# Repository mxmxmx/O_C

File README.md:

o_C. polymorphic CV generator
===

### firmware:

o_C is a collaborative project by Patrick Dowling (aka pld), mxmxmx and Tim Churches (aka bennelong.bicyclist) (though mostly by pld and bennelong.bicyclist). it **(considerably) extends** the original firmware for the o_C / ASR eurorack module, designed by mxmxmx.

### hardware:

eurorack / teensy 3.2 DAC8565 quad 16bit CV module w/ OLED display

14HP, depth ~ 25mm

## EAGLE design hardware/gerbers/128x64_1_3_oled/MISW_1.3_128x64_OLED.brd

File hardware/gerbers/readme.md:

CAM files for teensy 3.x quad 16 bit CV generator/processor
============

###gerbers for:

- O_C main pcb (2.e)
- SSD1306 / SH1106 OLED carrier pcb (thanks, altitude909)

###BOM for OLED carrier pcb

(all 0603): 

- 4 x 10k 
- 1 x 390K 
- 5 x 2.2uF (10V)
- 1 x 10uF (10V)

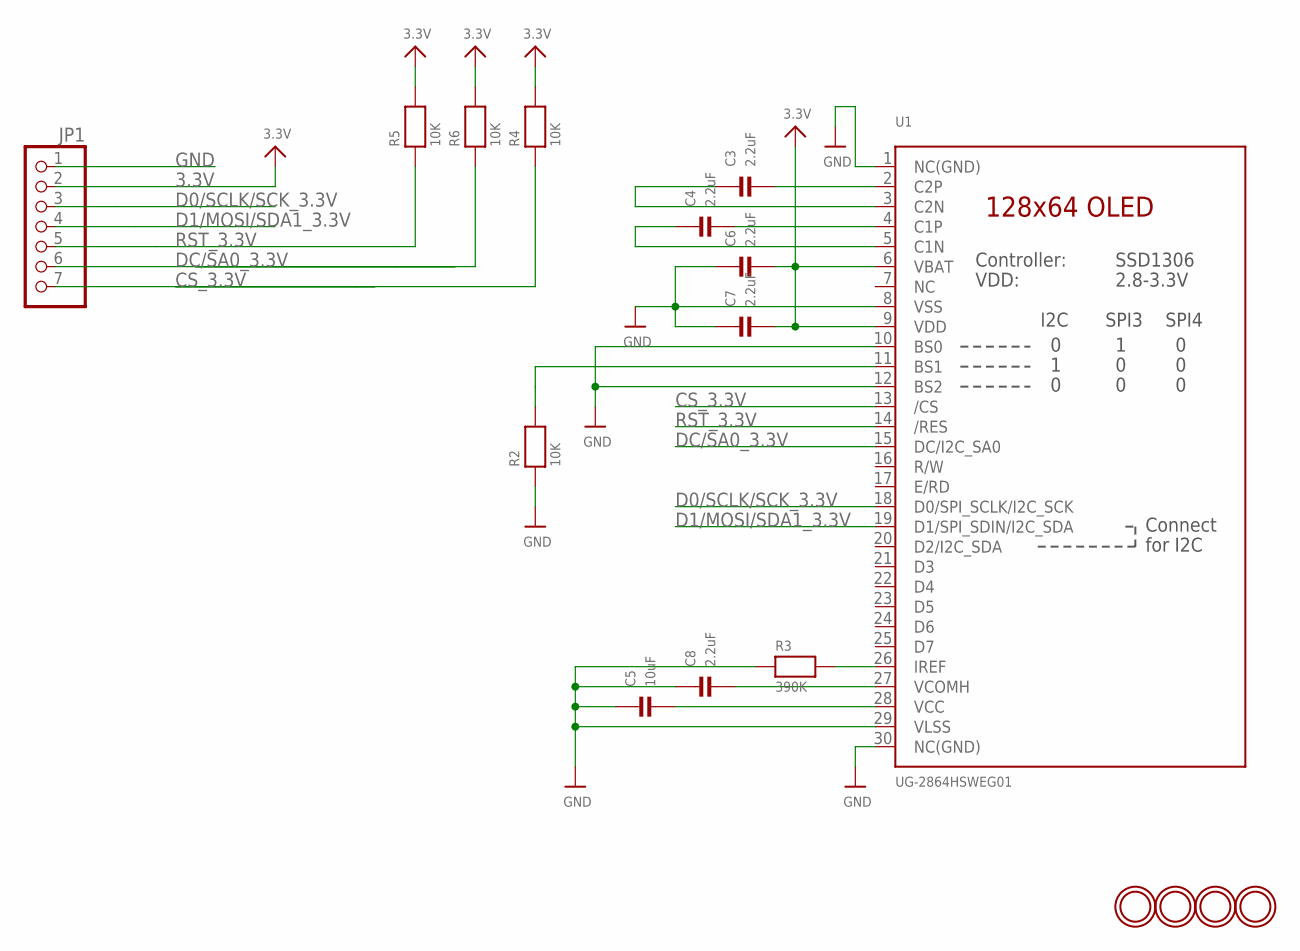
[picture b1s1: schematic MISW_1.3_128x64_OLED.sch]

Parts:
C3, C4, C6, C7, C8: 2.2uF; 0603-MINI
C5: 10uF; 0603-MINI
JP1: HEADER-1X7ROUND; 1X07_ROUND
R2, R4, R5, R6: 10K; 0603-MINI
R3: 390K; 0603-MINI
U1: UG-2864HSWEG01; UG-2864HSWEG01_1.3_WRAPAROUND
U$23, U$24, U$25, U$26: MOUNTINGHOLE2.5; MOUNTINGHOLE_2.5_PLATED

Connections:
3.3V: C6.2, C7.2, JP1.2, R4.2, R5.2, R6.2, U1.6 (VBAT), U1.9 (VDD)
CS_3.3V: JP1.7, R4.1, U1.13 (/CS)
D0/SCLK/SCK_3.3V: JP1.3, U1.18 (D0/SPI_SCLK/I2C_SCK)
D1/MOSI/SDA1_3.3V: JP1.4, U1.19 (D1/SPI_SDIN/I2C_SDA)
DC/SA0_3.3V: JP1.6, R6.1, U1.15 (DC/I2C_SA0)
GND: C5.1, C6.1, C7.1, C8.1, JP1.1, R2.1, R3.1, U1.1 (NC(GND)), U1.8 (VSS), U1.10 (BS0), U1.12 (BS2), U1.29 (VLSS), U1.30 (NC(GND))
unnamed: R2.2, U1.11 (BS1)
unnamed: R3.2, U1.26 (IREF)
unnamed: C3.2, U1.2 (C2P)
unnamed: C3.1, U1.3 (C2N)
unnamed: C4.2, U1.4 (C1P)
unnamed: C4.1, U1.5 (C1N)
unnamed: C5.2, U1.28 (VCC)
unnamed: C8.2, U1.27 (VCOMH)
RST_3.3V: JP1.5, R5.1, U1.14 (/RES)

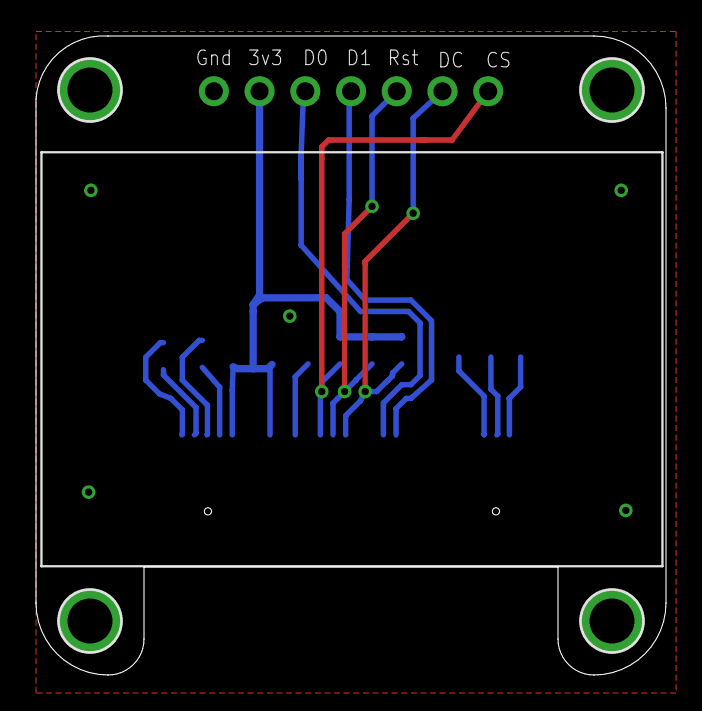
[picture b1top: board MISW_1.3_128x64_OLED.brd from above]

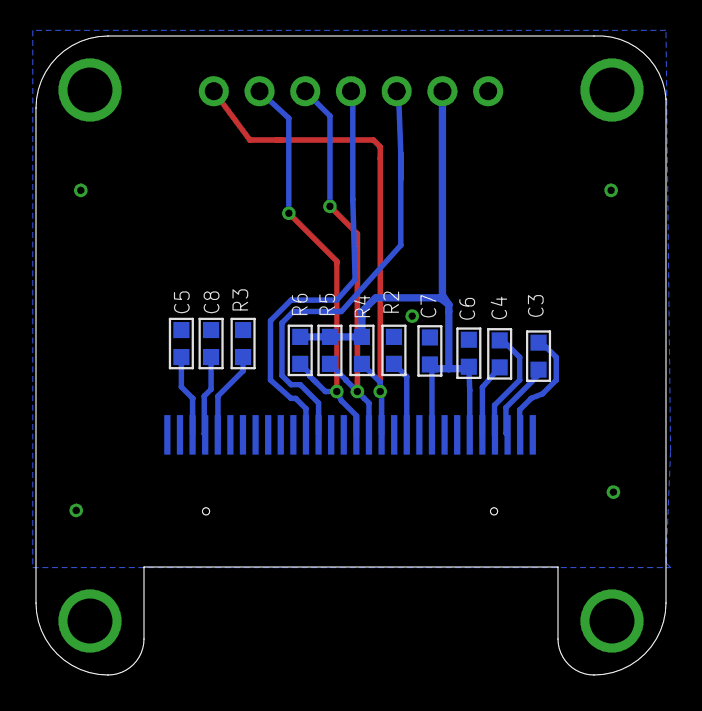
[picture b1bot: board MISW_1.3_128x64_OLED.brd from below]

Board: 2 copper layers, 35.0 x 35.5 mm, 17 parts (11 on the bottom side), 15 nets.

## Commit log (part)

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2017-03-27 Add Bohlen-Pierce scale
2017-03-27 [AC] clean-up
2017-03-27 [AC] trigger delay
2017-04-01 Further tweaks to micro/macrotonal scales
2017-04-02 [microtonal] Add lots of tritave scalings
2017-04-04 Add harmonic series scales for octave and tritave, and a Sevish 31-EDO scale
2017-04-04 More sen-harmonic scales
2017-04-06 Add quartertone support (of sorts)
2017-04-08 [IntSeq] Added a fractal sequence
2017-04-08 [ENVGEN] Tweak Eucl reset trigger input
2017-04-08 [ENVGEN] Add Euclidean reset clock divider setting
2017-04-08 [AC] editor
2017-04-08 [AC] directions
2017-04-08 Fix #if, cosmetic adjustments
2017-04-09 [AC] Added Brownian motion to directions, with prob setting
2017-04-09 Fix minor merge problems, bump version number
2017-04-09 [AC] preliminary progressions
2017-04-09 [AC] progressions prelim.
2017-04-09 [AC] playmodes
2017-04-09 [AC] S/H
2017-04-10 [1.36] integrate ADC.h, fix compiler warnings
2017-04-10 [README] formatting
2017-04-11 [REFS] Proof-of-concept of frequency measurement
2017-04-12 [REFS] Tweak
2017-04-13 [REF] move FreqMeasure
2017-04-14 [REFS] Updated frequency meter/tuner display
2017-04-14 [REFS] Add BPM display for low frequencies
2017-04-15 [POLYLFO] Still not working...
2017-04-15 [AC] temp fix
2017-04-15 [REF] fix conflict
2017-04-15 [REFs] internal pull ups
2017-04-15 [REF] margins
2017-04-16 [AC] CV
2017-04-17 [CLEAN UP] buchla/microtonal
2017-04-17 [AC] CV / menu
2017-04-17 [AC] display progression #
2017-04-17 [AC] downbutton -> CV mapping
2017-04-17 [SEQ] misc + toggle update
2017-04-17 [SEQ] add missing octave setting
2017-04-17 [SEQ] screensaver
2017-04-18 [AC] chords fix; [SEQ] store EoS update
2017-04-18 [ASR] refactoring (store raw pitch)
2017-04-18 [ASR] refactoring
2017-04-18 [1.36] FIX
2017-04-18 [ASR] fix ADC offsets
2017-04-19 [ASR] CV4 options
2017-04-19 [ASR] buflen
2017-05-04 [SEQ] ?
2017-05-04 [AUTO] basics
2017-05-05 [AUTO] menu basics
2017-05-05 [A11Z] Fix BUCHLA define
2017-05-05 Revert "Merge remote-tracking branch 'origin/v1.3-alpha' into v1.3-alpha"
    This reverts commit ba3894b82cc33a09a4c7003600558b971688da44, reversing
    changes made to 02f0b5352b493cea5ea7a6dcd63d704e9110c66d.
2017-05-05 [A11z] Fix BUCHLA_SUPPORT #ifdef
2017-05-06 [REFS] add ppqn to bpm display
2017-05-06 [AC] menu details; don't update chord when out-of-range
2017-05-06 [RESOLVE CONFLICTS]
2017-05-06 [POLYLFO] Fix conflict from stash
2017-05-06 [REFs] AT misc
2017-05-06 [POLYLFO] Working tap-tempo implementation
2017-05-06 [REFS] Add support for user-settable A above middle C tuning standard
    Defaults to the ISO standard of 440Hz, but anything between 400 and 480
    Hz to two decimal places can be specified. Calculation accuracy is also
    improved.
2017-05-07 [POLYLFO] tweak UI, add freq multipliers
2017-05-07 [BYTEBEATS] Bug fix - null CV assignments not properly handled.
2017-05-07 [REFs] resolve conflicts
2017-05-07 [BBgen] resolve conflict
2017-05-07 [BBgen] resolve conflicts
2017-05-07 [BBGEN] Fix unhandled null CV mapping bug
2017-05-07 [REFs] naive AT, take more time
2017-05-07 [REFs] average readings
2017-05-08 [REFs] converge faster / bisectional
2017-05-08 [POLYLFO] Tweak tap tempo algorithm cross-over point
2017-05-08 [REF] reset autotuner when done
2017-05-08 [REFs] close AT properly
2017-05-08 [REFs] clean up
2017-05-08 [REFs] arm AT with up button
2017-05-09 [REFs] start at 0V
2017-05-09 [REFs] remove redundant files
2017-05-09 [SEQ] [AC] details + [OC] prio
    (hopefully) fixes glitches with gcc 5.4
2017-05-09 [ASR] display delay type
2017-05-09 [DAC] remove print
2017-05-09 {IntSeq] Remove digits of phi sequence
2017-05-10 [POLYLFO] Show frequency/period on menu top line
2017-05-10 [MISC] make serial printing when loading/saving settings optional
2017-05-11 [SEQ] [DQ] remove PW string; [DEBUG] fix compiler warnings
2017-05-11 [DQ] root
2017-05-11 [DEBUG] #ifdef obsolete debug screens for apps
2017-05-11 [REFS] Suppress last/spurious freq measure if no TR4 input for > 100 seconds
2017-05-11 [DQ] transpose per slot; misc minor rationalizations
2017-05-11 [DQ] clean up
2017-05-13 Revert "Revert "Merge pull request #31 from mxmxmx/v.1.3-alpha_DQ""
    This reverts commit 631ca2d9c072aabf546bca320a7a43187ac1d996.
2017-05-13 [OC] move strings
2017-05-13 [scale edit] Correct min/max values when editing
2017-05-13 [SEQ] quick & dirty attempt at prettier editing
2017-05-13 [DQ] make edit behaviour more QQ like
2017-05-13 [SEQ] slight rearrangement of editor
2017-05-14 [AC] Fix base note display for microtonal scales
2017-05-14 [SEQ] editor
2017-05-14 [SEQ] move octave
2017-05-14 [ASR] Add input gain as a destination for CV4 input
2017-05-14 [ASR] adjust right-shift
2017-05-14 [SEQ] draw clock
2017-05-15 [OC] bump to 1.3 beta
2017-05-15 [SEQ] draw full scale name
2017-05-16 [OC] switch for 4U
2017-05-16 [OC] compile options
2017-05-16 [OC] 4U reset [DQ] scale change
2017-05-17 [OC] delete BOM
2017-05-19 [OC] bump version
2017-05-19 [ASR] make sure buffer isn't frozen
2017-05-20 [REFS] re-enable autotune DAC code debug if PRINT_DEBUG is defined
2017-05-20 [ASR] Rename M/A to igain in CV destinations for consistency
2017-05-20 [ASR] Adjust influence of ext CV on TM range parameter
2017-05-20 [ASR] at TM fix
2017-05-20 [OC] further incr. delay (input init)
2017-05-20 [DQ] edit root/transpose in editor [REFs] DAC limit error
2017-05-20 [DQ] root/transpose
2017-05-20 [REFs] throw error / DAC overflow
2017-05-21 [ASR] hack / fix freeze
2017-05-24 [OC] move scaling to DAC.h/cpp
2017-05-25 [OC] re-ordered alt. scalings
2017-05-25 [OC] 4U input cal. display
2017-05-25 [OC] remove redundant include
2017-05-28 [ENVGEN] Add maximum loops setting for looping envelopes
2017-05-28 [ENVGEN] Add CV control to number of loops for looping envelopes
2017-05-29 [ENVGEN] Adjustments to inverted envelopes, and boring app name support
2017-05-30 [ENVGEN] Fix menu length handling when optional items displayed
2017-05-31 [H1200] Fix settings storage problem due to use of U4 type
2017-06-03 [A11Z] Add trigger delay to A11Z
2017-06-03 [H1200] Fix trigger delay behaviour if CV sampling = Continuous
2017-06-03 [SEQ] gates
2017-06-03 [DAC] 4U
2017-06-04 [MISC] Bump version to v1.3-beta3
2017-06-04 [POLYLFO] Remove redundant LUTs, saves 2.5k of flash
2017-06-04 [OC] fix global alt.scaling
2017-06-04 [OC] scalings; return to scale editor
2017-06-05 [OC] debug clean-up
2017-06-05 [OC] debug
2017-06-05 [IntSeqs] Halve length of Integer Sequences to save flash storage
2017-06-05 [OC] alt. tunings / indicator
2017-06-05 [OC] disable debug
2017-06-06 [OC] alt. tunings; indicator tweak
2017-06-06 [OC] 4U / 10V
2017-06-07 [OC] move codebook centre
2017-06-07 [ENV] 4U range
2017-06-08 [SEQ; DQ] gates
2017-06-08 [SEQ/DQ] scale gates
2017-06-08 [4U] BB/ByteB
2017-06-09 [DQ] gates; transpose
2017-06-09 [DQ] fix ASR (cont. mode); disable TM (cont. mode)
2017-06-09 [QQ/DQ] fix int CV transpose
2017-06-09 [DQ] clean-up
2017-06-09 [4U] ByteB
2017-06-10 [ENVGEN] Add settable attack phase falling gate behaviour
    Fixes problem of ADSR and ASR envelope types flat-lining with fast
    triggers on default settings.
2017-06-10 [ENVGEN] Patrick Dowling's cross-channel end-of-cycle trigger modification
2017-06-10 [DQ/SEQ] 4U gates @ 10V
2017-06-10 [H1200] 4U octaves
2017-06-10 [ENVGEN] Center display of pattern, show position indicator
2017-06-10 [ENV] limit k, offset
2017-06-11 [ENVGEN, H1200] add length param to Euclidean rotate function
2017-06-11 [LORENZ] 4U
2017-06-11 [ANETZ] 4U
2017-06-13 [REFS] 4U
2017-06-13 [4U] fix define
2017-06-13 [4U] autocal
2017-06-13 [4U] autocal revert
2017-06-15 [POLYLFO] Fix phase/freq spread regression
2017-06-15 [ENV] don't overdo it
2017-06-16 [ENVGEN] reduce trigger delay due length; elaborate looping envelope types
2017-06-16 Bump version string to v1.3.1
2017-06-16 [ENVGEN] Hide Euclidean reset settings for now
2017-06-17 [ENVGEN] Remove inadvertently included hex files
2017-06-17 [ENVGEN] Fix suggested by Patrick for Euclid resets - but visualisation still not working when enabled
2017-06-17 [ENVGEN] Fix for Euclidean reset found by Patrick - works now
2017-06-17 [ENVGEN] Optimisation suggested by Patrick, plus fix Eucl reset storage type
2017-06-20 [REFS] Move floating point calcs out of ISR
2017-06-20 [REFs] spread float multiplications
2017-06-21 [REFs] round
2017-06-21 [SEQ] remove serial
2017-06-25 [POLYLFO] Add cascading cross-channel amplitude modulation
2017-06-25 [ENVGEN] First attempt at ASAR envelope type
2017-06-25 Revert "[ENVGEN] First attempt at ASAR envelope type"
    This reverts commit a8e2b2ad7786da662eece6928a2b573c112e680f.
2017-06-25 [POLYLFO] Fix the direction in which cross-channel AM works.
2017-06-27 [POLY] cv4
2017-06-27 [POLY] TR4: double F
2017-06-28 [POLY] TR4: 2x for all channels
2017-06-28 [POLY] TR4 choices
2017-06-29 [OC] bump to v1.3.2
2017-07-08 [SEQINS] Add voltage control to envelopes
2017-07-09 [SEQUINS] Add settings for env reset behaviour (in the CV menu)
2017-07-09 [SEQUINS] Addition of more clock divisors to permit easy "Piano Phase" pieces using one clock for both channels
2017-07-11 [SEQINS] Start of work on ratchetting
2017-07-12 Revert "[SEQUINS] Addition of more clock divisors to permit easy "Piano Phase" pieces using one clock for both channels"
    This reverts commit f77a04e0356d290d27396ff0d5ea86aaf9fff7f2.
2017-07-16 [H1200] Fix menu glitch
2017-07-22 [DIET] Rationalise integer sequences and scales further so it fits with gcc 4.8 (sob!)
2017-07-22 [H1200] re-fix menu glitch properly
2017-07-23 [SEQUINS] Add more divisors to permit Reichian piano phase
2017-07-29 Revert "[A11Z] Add seperate trigger delay for arp/strum"
    This reverts commit 006ce2aa63551c6dae547f1b8fdd9d7dca6c6e9c.
2017-07-29 [A11Z] Fix arp/strum modes - d'oh!
2017-07-29 [A11Z] Use separate delay lines for grid and arp/strum triggers
2017-07-29 [A11Z] Add strum inhibit flag
2017-07-30 [SEQ] init arp
2017-07-31 [SEQ] arp init
2017-08-06 [IntSeq] Re-instate two integer sequences that were dropped due to space squeeze (they fit OK).
2017-08-06 [OC] flip
2017-08-10 [FTM] reinit pin
2017-08-21 [AC] 1.38
2017-08-21 [AC] scale update
2017-08-21 [QUANTIZER] memcpy
2017-08-22 [QUANTIZER] tweaks
2017-08-24 [OC] version
2017-08-25 [QUANTIZER] inline; version
2017-09-09 Tweaks to Harrington encoder and button defaults
    L encoder changes inversion, buttons change octaves
2017-09-30 [ENVGEN] Align parameters with enum in call to apply_cv_mapping to avoid off-by-one
2017-10-05 [OC] cOC support
2017-10-13 [OC] cOC calibration
2017-10-18 Trigger long-press as soon as the button is held long enough, instead of at release
2017-12-27 cOC misc
2018-01-07 [ENVGEN] Fix off-by-one indexing into array
2018-01-27 Add option to invert display pixels
2018-01-31 Fix mapping between DigitalInput enum and physical pin This works in the regular case (since TR1-4 are pins 0-3) but fails when FLIP_180 is enabled (or if the physical pins are remapped)
2018-03-02 [OC] move DAC8564 to options
2018-04-04 [DQ] missing break
2018-04-04 [DQ] update
2018-06-10 Added Hello World app
2018-06-10 update version
2018-06-14 change method name
2018-06-14 Tutorial 2: Final
2018-06-16 Pong
2018-06-16 Pong - trigger on bounce instead of loss
2018-06-16 Pong, final(?)
2018-06-16 Pong: Change class name
2018-06-19 Add CV Inspector
2018-06-20 Darkest Timeline - minor refactor
2018-06-20 Darkest Timeline - screensaver fixes
2018-07-01 Add LFSR loop reset functionality to Quantermain
2018-07-02 Tutorial 5: Menus
2018-08-30 [ADC] use DMA
2018-08-30 [ADC] params
2018-09-09 [OC] pin voodoo
2018-09-10 [ADC] comment
2019-01-24 [OC] v1.35
2019-02-25 [ADC] FLIP_180
2019-03-10 [DAC] Vbias
2019-03-10 [DAC] rename
2019-04-25 [QQ] LFSR range CV src
2019-04-27 [cal] values
2019-04-28 [OCp] vbias-button
2019-05-19 [DQ] fix
2019-05-19 [DQ] cnt
2019-05-19 [DQ] seqmode
2019-05-19 [DQ] reset
2019-08-10 remove Eclipse project files
2019-08-10 Space/Newline Clean-up
2019-08-10 Remove project
2019-08-10 More minor cleanup
2019-09-12 [CAL] asym
2019-10-07 [VOR] ifdef
2019-10-09 [OC] hex size (disable scales)
2019-10-13 [OC] scales
2019-11-10 remove UI_MODE_APP_SETTINGS
    Cruft not intended to be included in the commit.
